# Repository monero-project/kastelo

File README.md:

# Kastelo
This is the project to create an official Monero Hardware Wallet

1. [Safe, Vault](https://en.wikipedia.org/wiki/Esperanto), a place to store valuables
2. An open hardware Monero wallet

## Are you a tester looking for FW?
Please go to firmware/monezor and read the README there

## Disclaimers
- No hardware available
- Currently in the design and pre-fabrication stage

## Documentation
- Project documentation is being written
- [Moneropedia](https://getmonero.org/knowledge-base/moneropedia/) is recommended for a general introduction to the Monero-verse

## Developers
- Contributing advice is found in CONTRIBUTING.md (please review before submitting a pull request)

### Project Management
Follow the engineering pace of our project at:

[https://taiga.getmonero.org/project/michael-rfc-hwallet-1-implementation/](https://taiga.getmonero.org/project/michael-rfc-hwallet-1-implementation/)

## Support
- IRC: [Freenode](irc://chat.freenode.net/#monero-hardware/)
- [Monero StackExchange](https://monero.stackexchange.com/)
- [Mattermost](https://mattermost.getmonero.org/monero/channels/monerohardware/)

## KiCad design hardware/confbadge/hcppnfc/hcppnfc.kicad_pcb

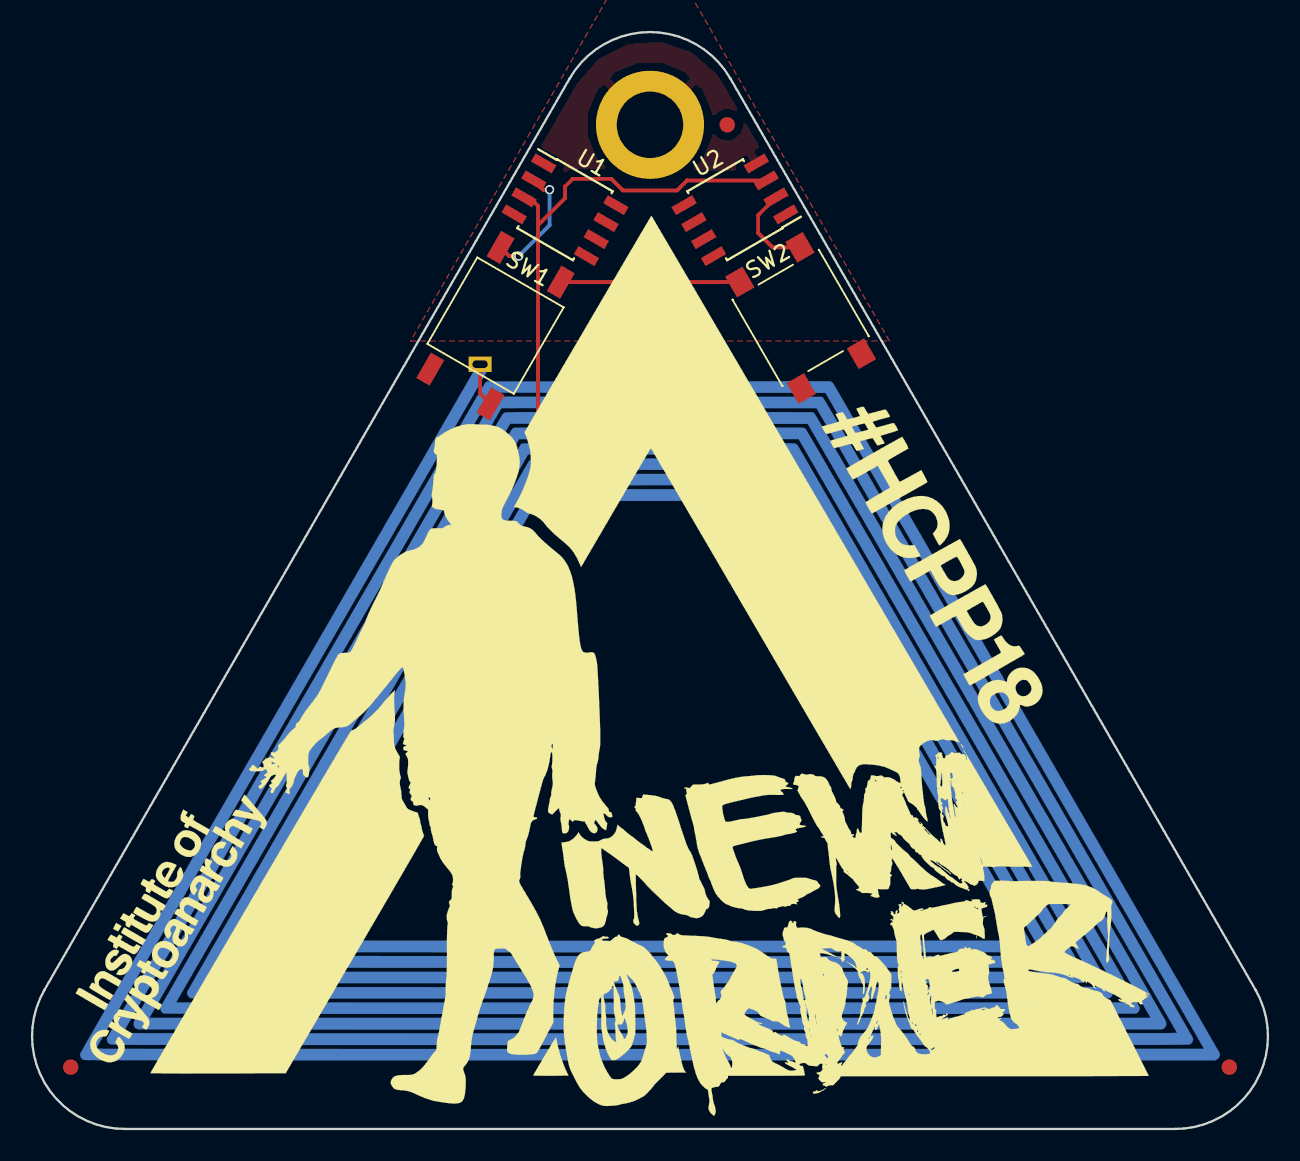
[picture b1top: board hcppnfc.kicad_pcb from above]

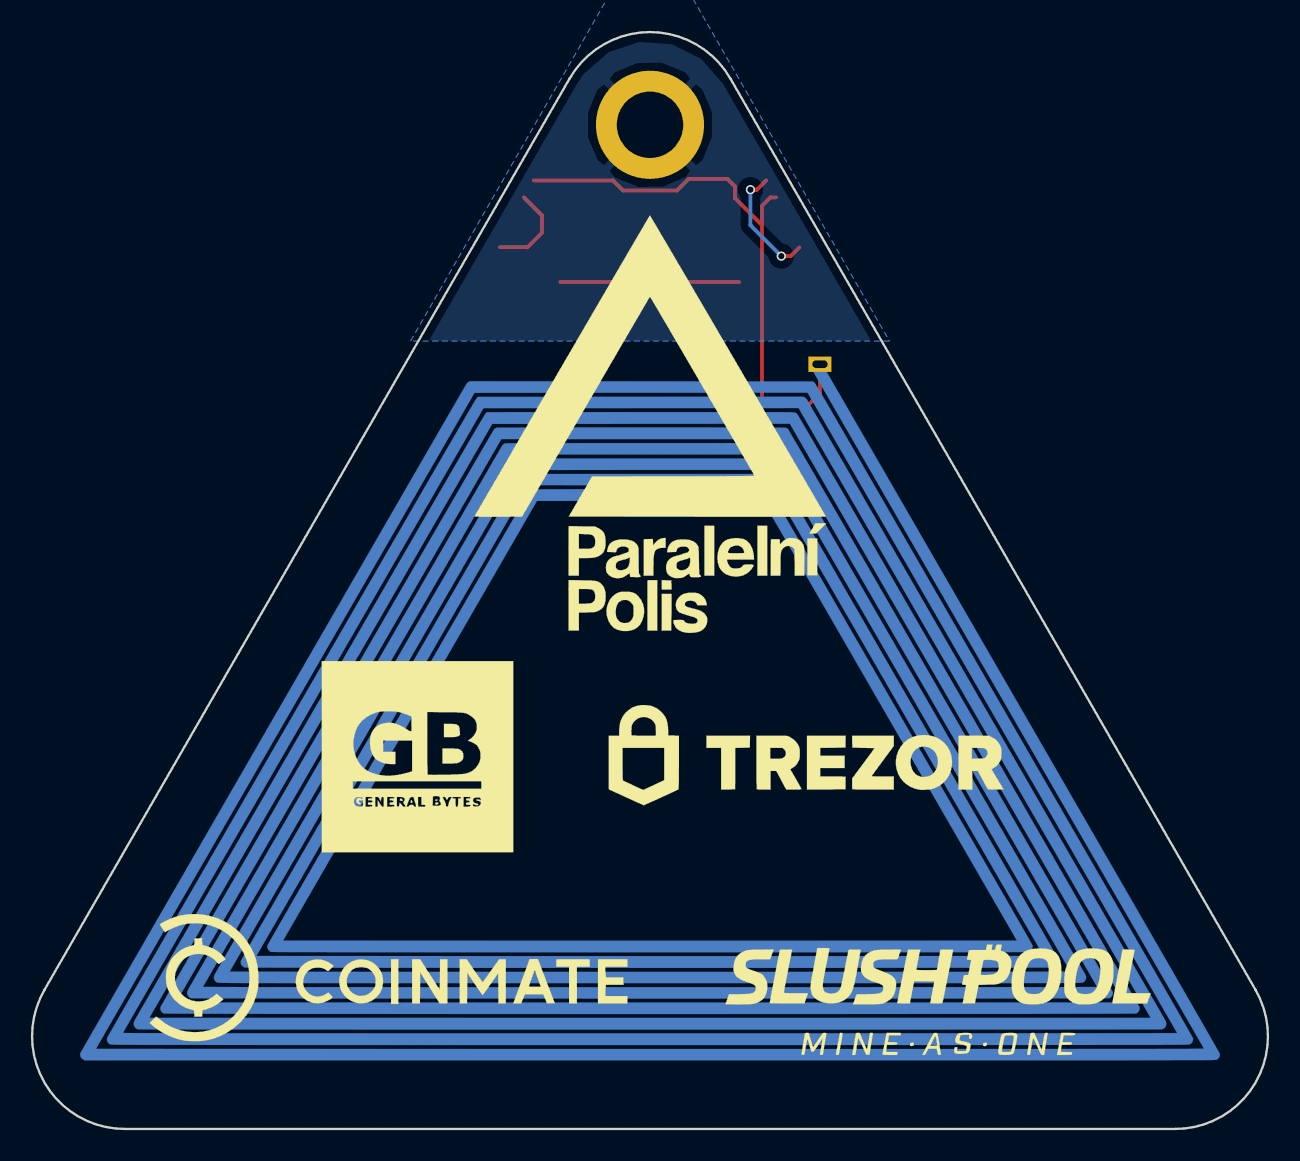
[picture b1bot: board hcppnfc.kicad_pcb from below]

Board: 2 copper layers, 80.0 x 71.0 mm, 13 parts (2 on the bottom side), 6 nets.

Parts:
AE1: Antenna_Loop; NFCAntennatall
FID1, FID2, FID3: Dummy_FIDUCIAL_Passermarke_Type1_RevE_Date16Nov20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; Fiducial_1mm_Dia_2mm_Outer
GFX*: ART_TRIANGLE; HCPPNewordtri
GFX*#2: ART_CONFYEAR; HCPPNewordconf
GFX*#3: ART_INSTCRYP; HCPPNewordinst
LOGO*: LOGO; HCPPSponsors
MH1: DUMMY_MOUNTING-HOLE_RevE_Date22jun2010; MountingHole_4.3mm_M4_ISO14580_Pad
SW1: SW_SPST; SW_SPST_K21102SP
SW2: SW_SPST; SW_SPST_PTS645
U1, U2: M24SR02-YMN; SOIC-8_3.9x4.9mm_Pitch1.27mm

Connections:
/ANTCON: AE1.2, U1.3, U2.3
GND: MH1.1, U1.4, U2.4
unnamed: AE1.1, SW1.1, SW2.1
unnamed: SW1.2, U1.2
unnamed: SW2.2, U2.2
VCC: U1.8, U2.8

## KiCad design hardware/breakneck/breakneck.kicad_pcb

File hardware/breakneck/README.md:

# Hardware Breakneck Design

The Breakneck design includes rich features as expected in a developer edition hardware wallet.

## Getting Started

The Breakneck design consists of several files, some which are not tracked in revision control but are part of [project releases](https://github.com/monero-project/kastelo/releases/).

* breakneck.pro (KiCad project)
* breakneck.sch (KiCad schematic)
* breakneck.kicad_pcb (KiCad layout)
* libraries (KiCad libraries)

Fabrication subdirectories contain files meant for printing, assembly, and other production work.

* billofmat (Bill of materials generated from breakneck.sch)
* fabpanel (Gerber files for printing panelized PCBs)
* fabraster (3D rendition of a single PCB layout)
* fabsingle (Gerber files for printing single PCBs)
* fabvector (Vector files useful for mechanical engineering)

Other subdirectories exist to provide conveniently formatted files generated from source.

* release (Tested distribution release files containing change logs)
* schematic (Copy of breakneck.sch converted to common graphic formats)

A Makefile serves project management tasks allowing for scripting and automation.

* Makefile (A GNU Makefile facilitating command line project tasks)

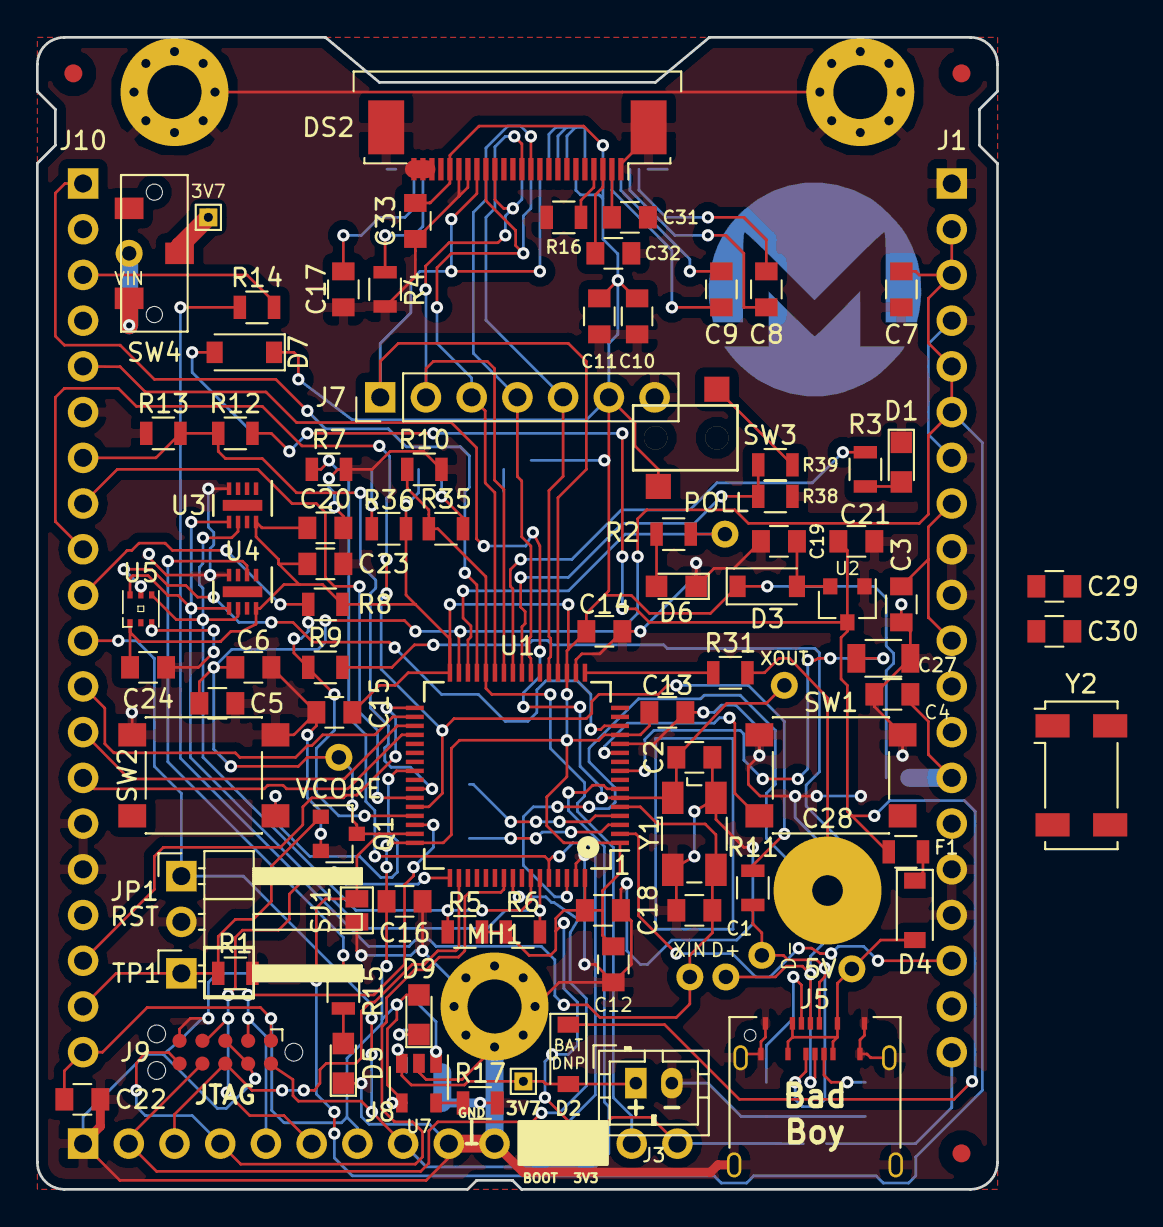
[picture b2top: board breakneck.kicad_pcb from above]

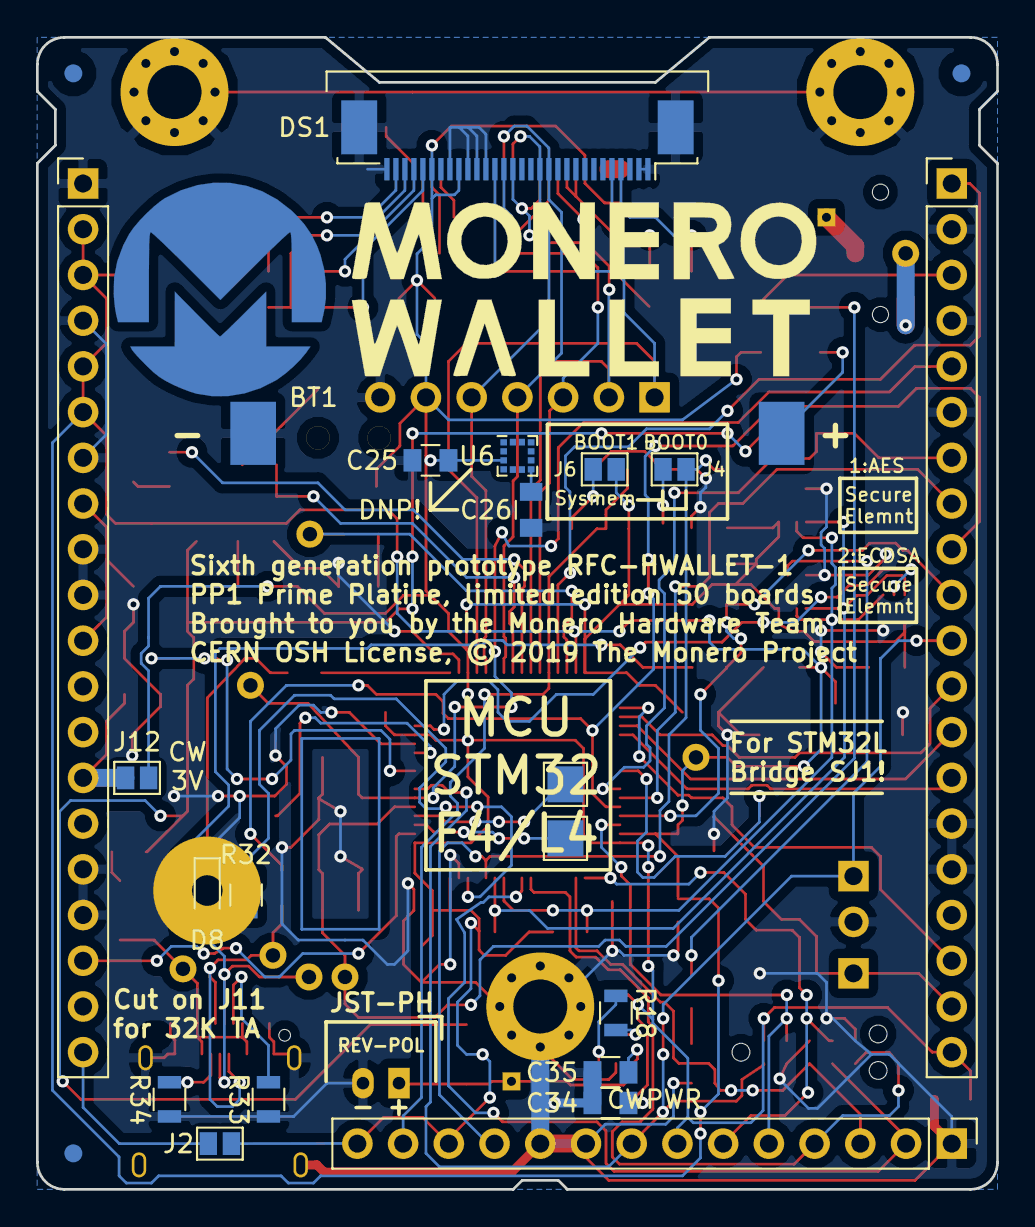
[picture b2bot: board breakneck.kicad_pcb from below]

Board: 2 copper layers, 53.3 x 64.0 mm, 124 parts (25 on the bottom side), 80 nets.

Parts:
3V7, 3V7#2: 3V7; TestPoint_THTPad_1.0x1.0mm_Drill0.5mm
5V: 5V; Measurement_Point_Round-TH_Small
BT1: Battery_Cell; Keystone_1058_1x2032-CoinCell
C1, C2: 12pF; C_0805
C3, C4, C7, C10, C12, C13, C14, C15, C16, C18, C20, C22, C23, C24, C25, C26: 100nF; C_0805
C5, C6, C17, C31: 2.2uF; C_0805
C8, C9, C11, C19, C21, C33: 1uF; C_0805
C27: 47nF; C_1206
C28: SW_Captouch; Captouch_Backlight_Circle_6mm
C29, C30: 4.3pF; C_0805
C32, C34, C35: 4.7uF; C_0805
D1: YELLOW; LED_0805
D2, D3, D4, D7: D_Schottky; D_SOD-123
D5: RED; LED_0805
D6, D9: LED; LED_0805
D8: WHITE; LED_0805
D+: DATA+; Measurement_Point_Round-TH_Small
D-: DATA-; Measurement_Point_Round-TH_Small
DS1: SSD1306; Eastrising_ER-CON30HT-1_01x30_P0.50mm
DS2: ER-CON24; Eastrising_ER-CON24HT-1_01x24_P0.50mm
F1: PTC; R_0805
FID1, FID2, FID3, FID4, FID5, FID6: Fiducial-PCB; Fiducial_1mm_Dia_2.54mm_Outer_CopperTop
J1: CONN_EAST; Pin_Header_Straight_1x20_Pitch2.54mm
J2, J4, J6, J12: GS2
J3: CONN_01X02; JST_PH_B2B-PH-K_02x2.00mm_Straight
J5: USB_C_Rcpt_Min; USBC_Rcpt_Min_12401610E4-2A
J7: CONN_OLED; Socket_Strip_Straight_1x07_Pitch2.54mm
J8: CONN_SOUTH; Pin_Header_Straight_1x14_Pitch2.54mm
J9: CONN_JTAG; Tag-Connect_TC2050-IDC-NL
J10: CONN_WEST; Pin_Header_Straight_1x20_Pitch2.54mm
JP1: Jumper; Pin_Header_Angled_1x02_Pitch2.54mm
LOGO1: Monerologo-mid; MoneroCircleCombi
MH1, MH2, MH3: Mountinghole-440; MountingHole_3mm_Pad_Via
POLL: TEST; Measurement_Point_Round-TH_Small
Q1: MOSFET; SOT-23
R1, R7, R10: 10K; R_0805
R2, R3, R15, R32: 150; R_0805
R4, R16: 390K; R_0805
R5, R6: 3.9K; R_0805
R8: 1.5K; R_0805
R9, R11: 22; R_0805
R12: 12K; R_0805
R13: 22K; R_0805
R14: 100; R_0805
R17: 2K; R_0805
R18: 470; R_0805
R31: 1K; R_0805
R33, R34: 5.1K; R_0805
R35, R36, R39: 510; R_0805
R38: 100K; R_0805
REF7, REF8: TestPoint_Pad_2.0x2.0mm
SJ1: Solderjumper; GS2
SW1, SW2: SW_SPST; SW_SPST_PTS645
SW3: SW_SPST; SW_SPST_ESE11MV1
SW4: SW_SPDT; SW_SPDT_CLSB-12A
TP1: GLITCH; Pin_Header_Angled_1x01_Pitch2.54mm
U1: STM32F405RGTx; LQFP-64_10x10mm_Pitch0.5mm
U2: LN6206P33M_SOT23; SOT-23
U3: ATECC608A; DFN-8-1EP_2x3mm_Pitch0.5mm
U4: ATAES132A; DFN-8-1EP_2x3mm_Pitch0.5mm
U5: LTR303ALS; ChipLED-6_2x2mm
U6: BMA280; LGA-12_2x2mm_P0.5mm
U7: MCP73831-2-OT; SOT-23-5
VCORE: VCORE; Measurement_Point_Round-TH_Small
VIN: VIN; Measurement_Point_Round-TH_Small
XIN: CRYSTIN; Measurement_Point_Round-TH_Small
XOUT: CRYSTOUT; Measurement_Point_Round-TH_Small
Y1: Crystal_GND24; Crystal_SMD_Abracon_ABM3B-4pin_5.0x3.2mm
Y2: Crystal; Crystal_SMD_Abracon_ABS25-4Pin_8.0x3.8mm

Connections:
+1V2: C5.1, C6.1, C7.1, J1.2, J1.3, J1.5, J1.6, Q1.3, SJ1.1, U1.31, U1.47, VCORE.1
+3V3: C10.1, C11.1, C12.1, C13.1, C14.1, C15.1, C16.1, C18.1, C20.1, C22.1, C23.1, C24.1, C25.1, C26.2, C33.1, C34.1, D3.1, D7.1, D9.2, DS1.6, DS1.9, DS2.5, J2.2, J6.2, J7.6, J8.7, J8.12, J8.14, J9.1, J10.20, J12.2, R5.1, R6.1, R8.2, R36.1, SW3.2, U1.1, U1.13, U1.19, U1.32, U1.48, U1.64, U3.8, U4.8, U5.1, U6.3, U6.7, U6.11, U7.4
+5V: C21.1, D2.1, F1.1, R12.2, U2.3
/BLOAD: J4.2, J8.11, R7.1, U1.60
/CTCH: R31.1, U1.17
/CTLED: R32.1, U1.62
/CTSMP: C27.1, U1.9
/GLITCH: J10.19, Q1.1, R1.1, TP1.1
/I2C_SCL: R5.2, U1.58, U3.6, U4.6, U5.4, U6.12
/I2C_SDA: R6.2, U1.59, U3.5, U4.5, U5.6, U6.2
/INT1: U1.15, U6.5
/INT2: U1.16, U6.6
/JTAG_TCK: J8.6, J9.4, U1.49
/JTAG_TDI: J8.3, J9.8, U1.50
/JTAG_TDO: J8.4, J9.6, U1.55
/JTAG_TMS: J8.5, J9.2, U1.46
/JTAG_TRST: J8.2, J9.7, U1.56
/OLED_D0: DS1.18, DS2.13, J7.5, U1.21
/OLED_D1: DS1.19, DS2.14, J7.4, U1.23
/OLED_DC: DS1.15, DS2.10, J7.2, U1.26
/OLED_~CS~: DS1.13, DS2.8, J7.1, U1.20
/OLED_~RES~: DS1.14, DS2.9, J7.3, U1.27
/OSC_IN: C1.1, R14.2, U1.5, XIN.1, Y1.3
/OSC_OUT: C2.2, J10.5, U1.6, XOUT.1, Y1.1
/RESET: J8.8, J9.10, J10.11, JP1.1, U1.7
/SPI_CS: J10.18, U1.33
/SPI_MISO: J10.13, U1.35
/SPI_MOSI: J10.14, U1.36
/SPI_SCK: J10.12, U1.34
/UART_RX: J10.8, U1.43
/UART_TX: J10.7, R12.1, R13.2, U1.42
/USB_N: J10.9, R11.2, U1.44
/USB_P: J10.10, R8.1, R9.2, U1.45
GND: BT1.2, C1.2, C2.1, C3.1, C4.1, C5.2, C6.2, C7.2, C10.2, C11.2, C12.2, C13.2, C14.2, C15.2, C16.2, C17.2, C18.2, C19.2, C20.2, C21.2, C22.2, C23.2, C24.2, C25.2, C26.1, C27.2, C29.2, C30.2, C31.2, C32.2, C33.2, C34.2, C35.2, D1.1, D5.1, D6.1, D8.1, DS1.1, DS1.8, DS1.10, DS1.11, DS1.12, DS1.29, DS1.30, DS2.1, DS2.2, DS2.3, DS2.6, DS2.7, DS2.24, J1.1, J1.4, J1.7, J1.9, J1.10, J1.16, J1.17, J3.2, J5.A1, J5.A12, J5.B1, J5.B12, J5.S1, J7.7, J8.1, J8.9, J8.10, J9.3, J9.5, J9.9, J10.2, J10.4, J10.6, J10.15, J10.16, JP1.2, MH1.1, MH2.1, MH3.1, Q1.2, R1.2, R4.1, R7.2, R10.2, R13.1, R16.2, R17.2, R33.1, R34.1, R38.2, SJ1.2, SW1.1, SW2.1, U1.12, U1.18, U1.63, U2.1, U3.4, U4.4, U5.3, U6.1, U6.8, U6.9, U7.2, Y1.2, Y1.4
unnamed: BT1.1, D7.2
unnamed: C3.2, J1.8, J1.11
unnamed: C4.2, J1.14, J12.1
unnamed: C8.1, DS1.2
unnamed: C8.2, DS1.3
unnamed: C9.1, DS1.4
unnamed: C9.2, DS1.5
unnamed: C17.1, DS1.27
unnamed: C19.1, D3.2, U2.2
unnamed: C28.1, R31.2
unnamed: C29.1, REF8.1, U1.3, Y2.1
unnamed: C30.1, REF7.1, U1.4, Y2.2
unnamed: C31.1, DS2.23
unnamed: C32.1, DS2.22
unnamed: C35.1, J3.1, SW4.3, U7.3
unnamed: D1.2, R3.2
unnamed: 3V7.1, 3V7#2.1, D2.2, SW4.2
unnamed: D4.1, F1.2
unnamed: 5V.1, D4.2, J5.A4, J5.A9, J5.B4, J5.B9
unnamed: D5.2, R15.2
unnamed: D6.2, R2.1
unnamed: D8.2, R32.2
unnamed: D9.1, R18.2
unnamed: DS1.26, R4.2
unnamed: DS2.21, R16.1
unnamed: J1.18, U1.2
unnamed: J1.20, J2.1
unnamed: J4.1, R36.2
unnamed: J5.A5, R33.2
unnamed: D+.1, J5.A6, J5.B6, R9.1
unnamed: D-.1, J5.A7, J5.B7, R11.1
unnamed: J5.B5, R34.2
unnamed: J6.1, R35.2
unnamed: J8.13, R10.1, R35.1, U1.28
unnamed: J10.1, U1.29
unnamed: J10.3, R14.1
unnamed: POLL.1, R2.2, U1.30
unnamed: R3.1, U1.25
unnamed: R15.1, U4.2
unnamed: R17.1, U7.5
unnamed: R18.1, U7.1
unnamed: R38.1, R39.2, U1.24
unnamed: R39.1, SW3.1
unnamed: SW1.2, U1.11
unnamed: SW2.2, U1.40
unnamed: U1.14, U5.5

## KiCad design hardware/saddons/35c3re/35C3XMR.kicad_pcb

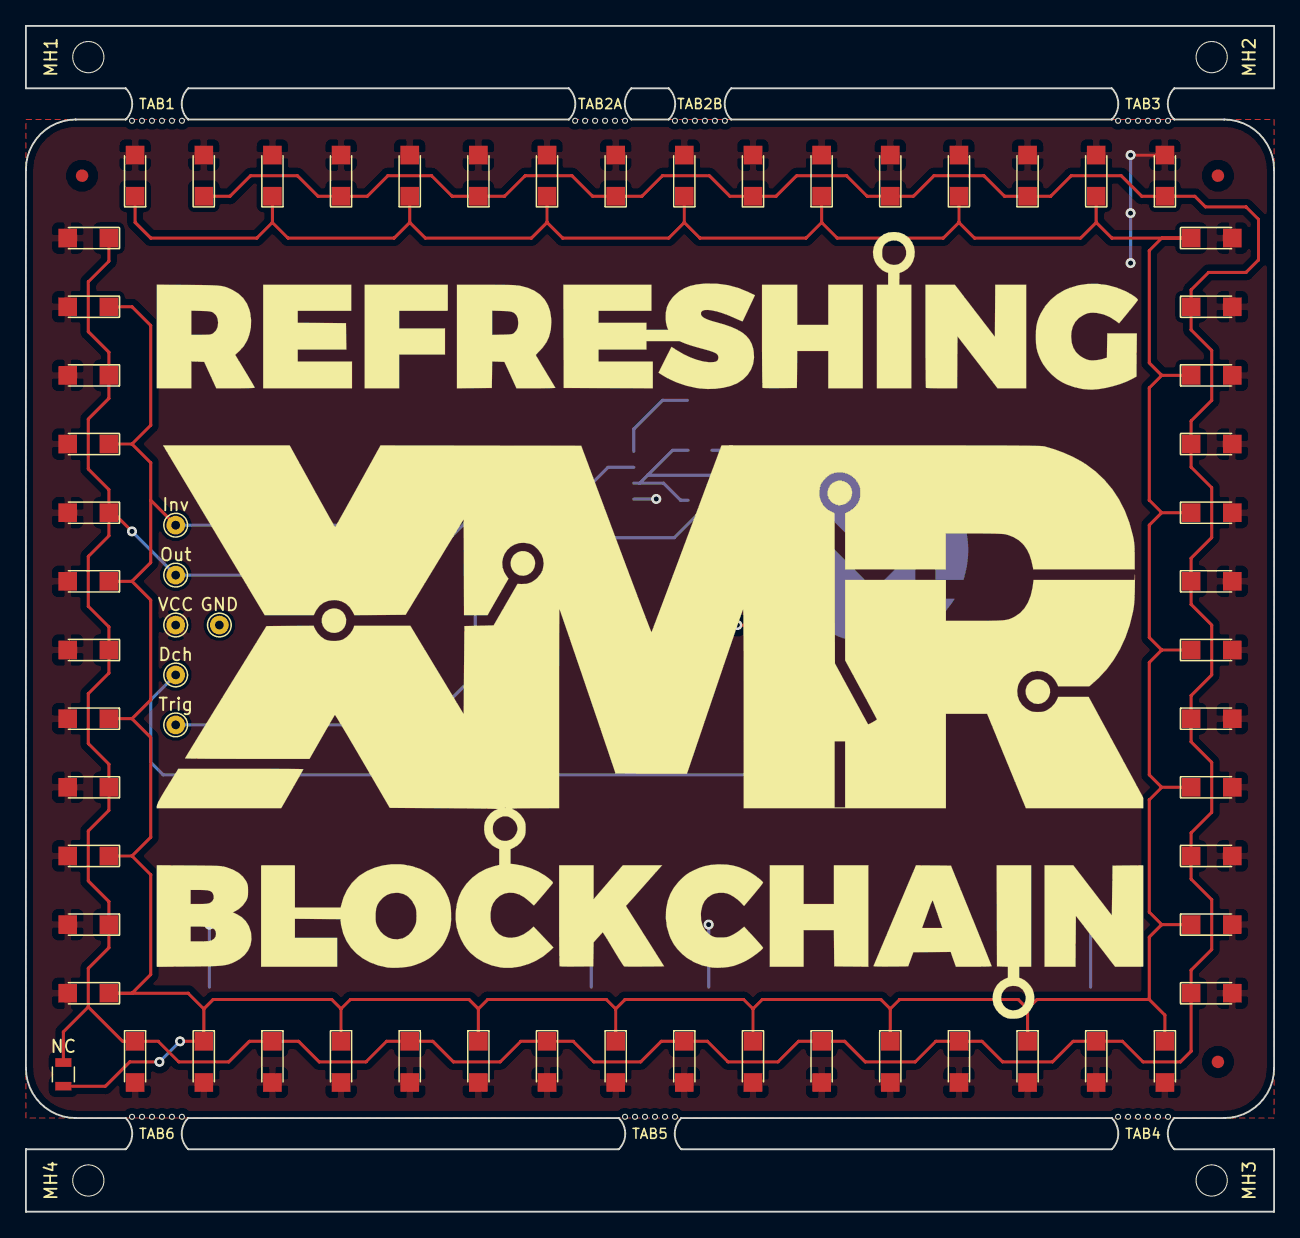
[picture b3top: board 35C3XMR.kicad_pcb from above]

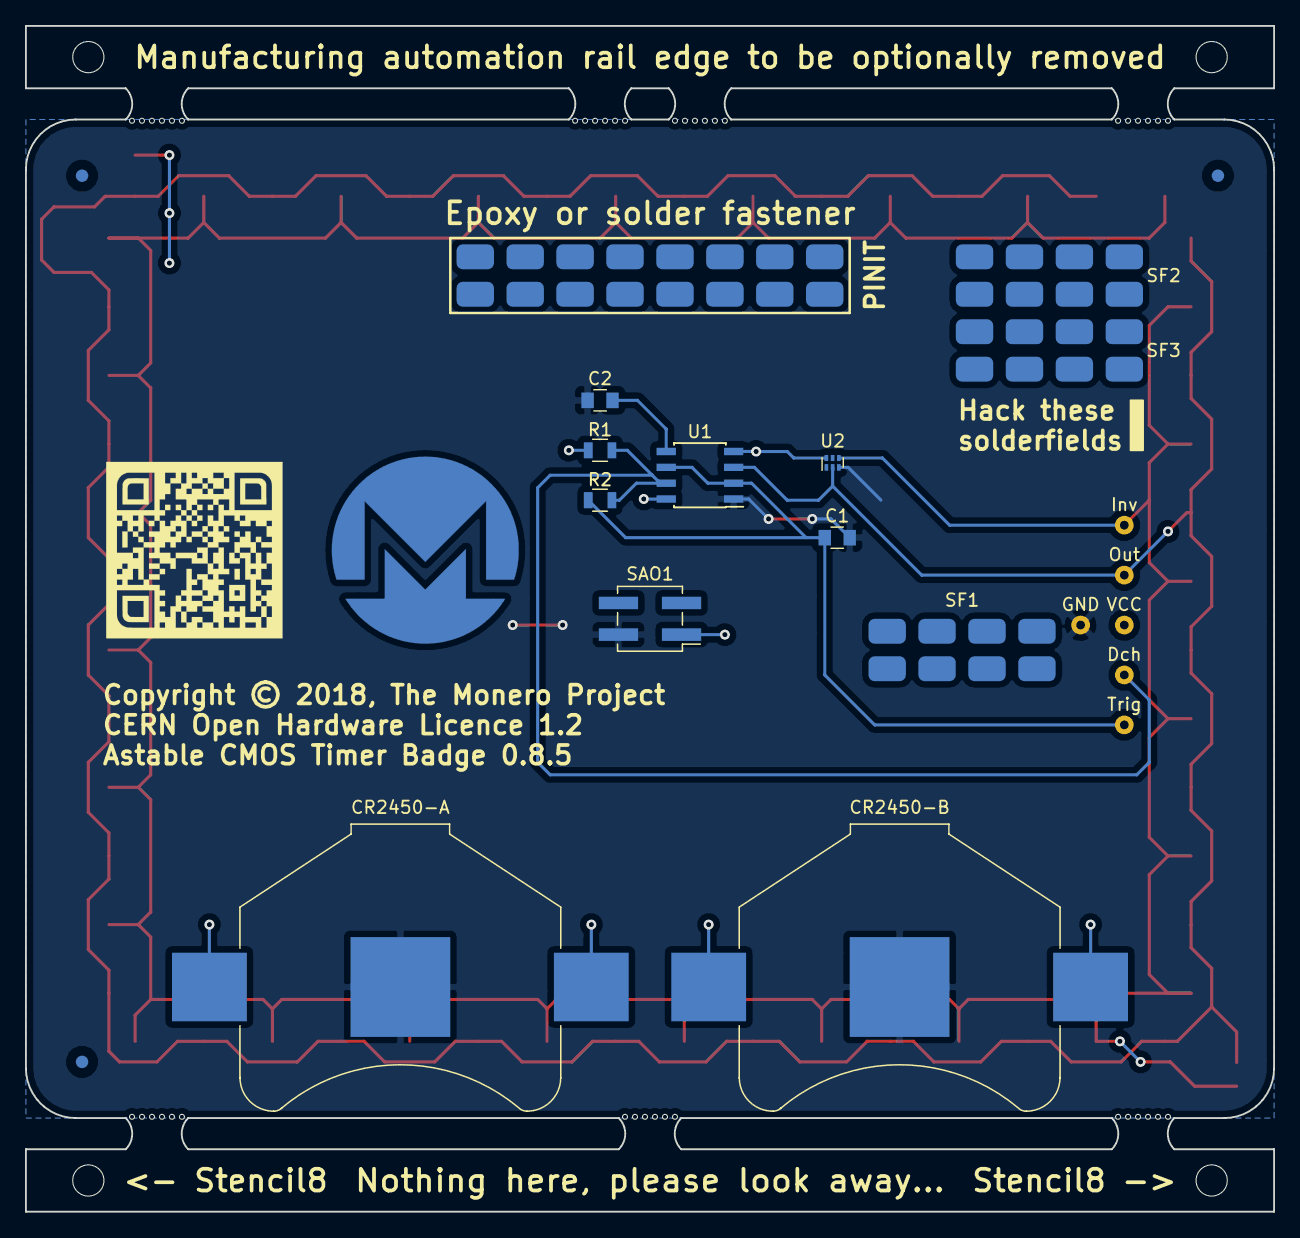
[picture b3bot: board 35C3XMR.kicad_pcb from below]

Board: 2 copper layers, 100.0 x 95.0 mm, 97 parts (19 on the bottom side), 7 nets.

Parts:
C1: 4,7uF; C_0805
C2: ,01uF; C_0805
CR2450-A, CR2450-B: Battery_Cell; BatteryHolder_Keystone_3008_1x2450
D1, D2, D3, D4, D5, D6, D7, D8, D9, D10, D11, D12, D13, D14, D15, D16, D17, D18, D19, D20, D21, D22, D23, D24, D25, D26, D27, D28, D29, D30, D31, D32, D33, D34, D35, D36, D37, D38, D39, D40, D41, D42, D43, D44, D45, D46, D47, D48, D49, D50, D51, D52, D53, D54, D55, D56: LED; LED_1206
Dch: TEST; TestPoint_THTPad_D1.5mm_Drill0.7mm
FID1, FID3, FID5: FiducialPassermarke-Top; Fiducial_1mm_Dia_2.54mm
FID2, FID4, FID6: FiducialPassermarke-Bot; Fiducial_1mm_Dia_2.54mm
G1: QRCOD; Kastelospecsqr
GND: TEST; TestPoint_THTPad_D1.5mm_Drill0.7mm
Inv: TEST; TestPoint_THTPad_D1.5mm_Drill0.7mm
LOGO1: 35C3Logo-funny; 35C3Funny
LOGO2: Moneroball; Moneroball_15mm
MH1, MH2, MH3, MH4: MountingHole_2.5mm
NC: Jumper; R_0805
Out: TEST; TestPoint_THTPad_D1.5mm_Drill0.7mm
R1: 10K; R_0805
R2: 100K; R_0805
SAO1: Shitty_conn; PinHeader_2x02_P2.54mm_Vertical_SMD
SF1, SF2, SF3, SF4, SF5: Soldfeld; Solderarea
TAB1, TAB2A, TAB2B, TAB3, TAB4, TAB5, TAB6: Panel_Mousetab_25mm_Single
Trig: TEST; TestPoint_THTPad_D1.5mm_Drill0.7mm
U1: TLC555; SOIC-8_3.9x4.9mm_P1.27mm
U2: NC7SZ04L6X; Fairchild_MicroPak-6_1.0x1.45mm_P0.5mm
VCC: TEST; TestPoint_THTPad_D1.5mm_Drill0.7mm

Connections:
+3V3: CR2450-A.1, CR2450-B.1, D1.2, D2.2, D3.2, D4.2, D5.2, D6.2, D7.2, D8.2, D9.2, D10.2, D11.2, D12.2, D13.2, D14.2, D15.2, D16.2, D17.2, D18.2, D19.2, D20.2, D21.2, D22.2, D23.2, D24.2, D25.2, D26.2, D27.2, D28.2, D29.2, D30.2, D31.2, D32.2, D33.2, D34.2, D35.2, D36.2, D37.2, D38.2, D39.2, D40.2, D41.2, D42.2, D43.2, D44.2, D45.2, D46.2, D47.2, D48.2, D49.2, D50.2, D51.2, D52.2, D53.2, D54.2, D55.2, D56.2, R1.2, SAO1.1, U1.4, U1.8, U2.6, VCC.1
GND: C1.2, C2.2, CR2450-A.2, CR2450-B.2, GND.1, SAO1.2, U1.1, U2.3
unnamed: C1.1, R2.2, Trig.1, U1.2, U1.6
unnamed: C2.1, U1.5
unnamed: D1.1, D3.1, D5.1, D7.1, D9.1, D11.1, D13.1, D15.1, D17.1, D19.1, D21.1, D23.1, D25.1, D27.1, D29.1, D31.1, D33.1, D35.1, D37.1, D39.1, D41.1, D43.1, D45.1, D47.1, D49.1, D51.1, D53.1, D55.1, Inv.1, NC.2, U2.4
unnamed: D2.1, D4.1, D6.1, D8.1, D10.1, D12.1, D14.1, D16.1, D18.1, D20.1, D22.1, D24.1, D26.1, D28.1, D30.1, D32.1, D34.1, D36.1, D38.1, D40.1, D42.1, D44.1, D46.1, D48.1, D50.1, D52.1, D54.1, D56.1, NC.1, Out.1, U1.3, U2.2
unnamed: Dch.1, R1.1, R2.1, U1.7

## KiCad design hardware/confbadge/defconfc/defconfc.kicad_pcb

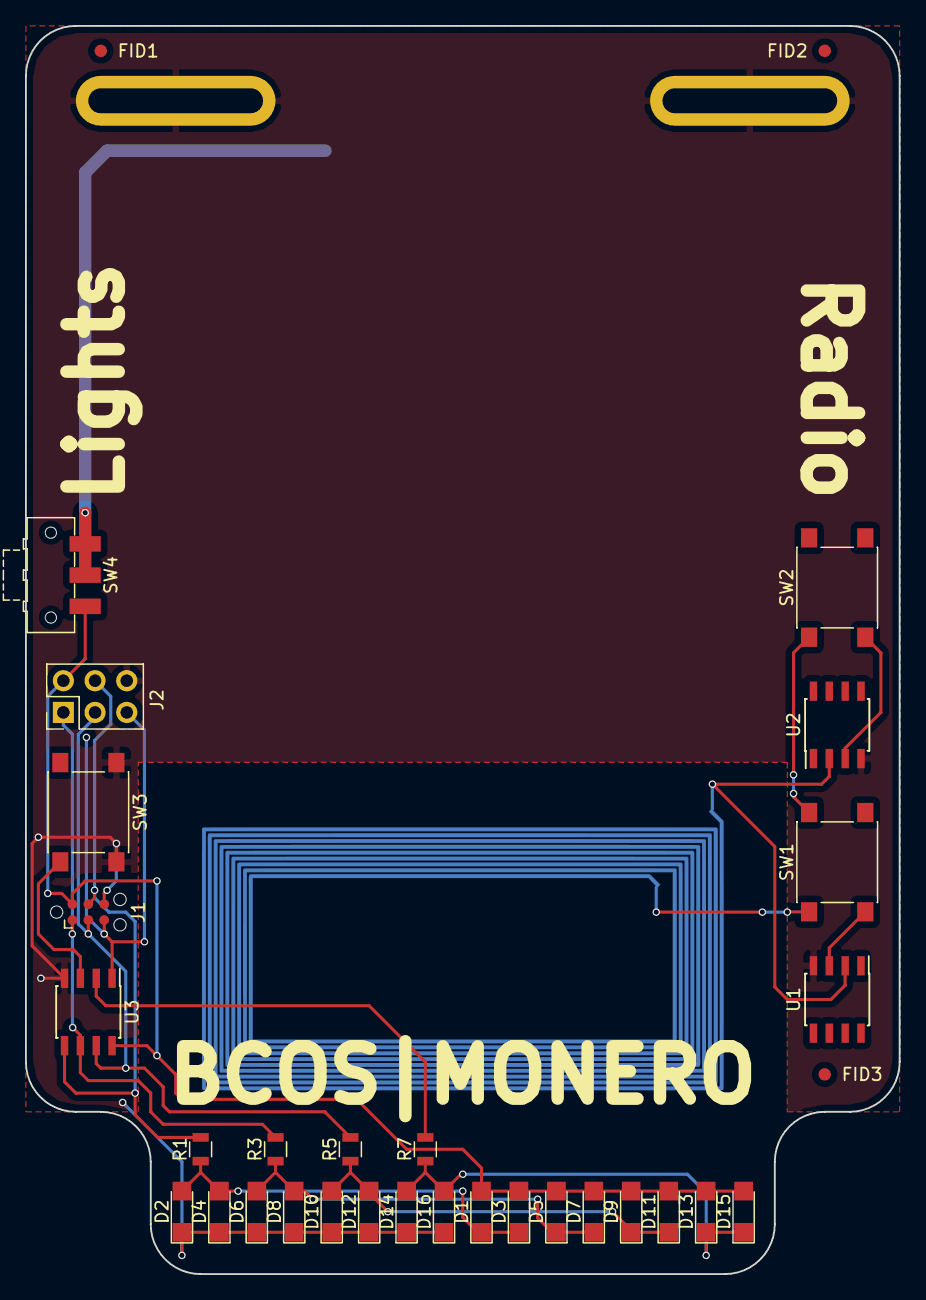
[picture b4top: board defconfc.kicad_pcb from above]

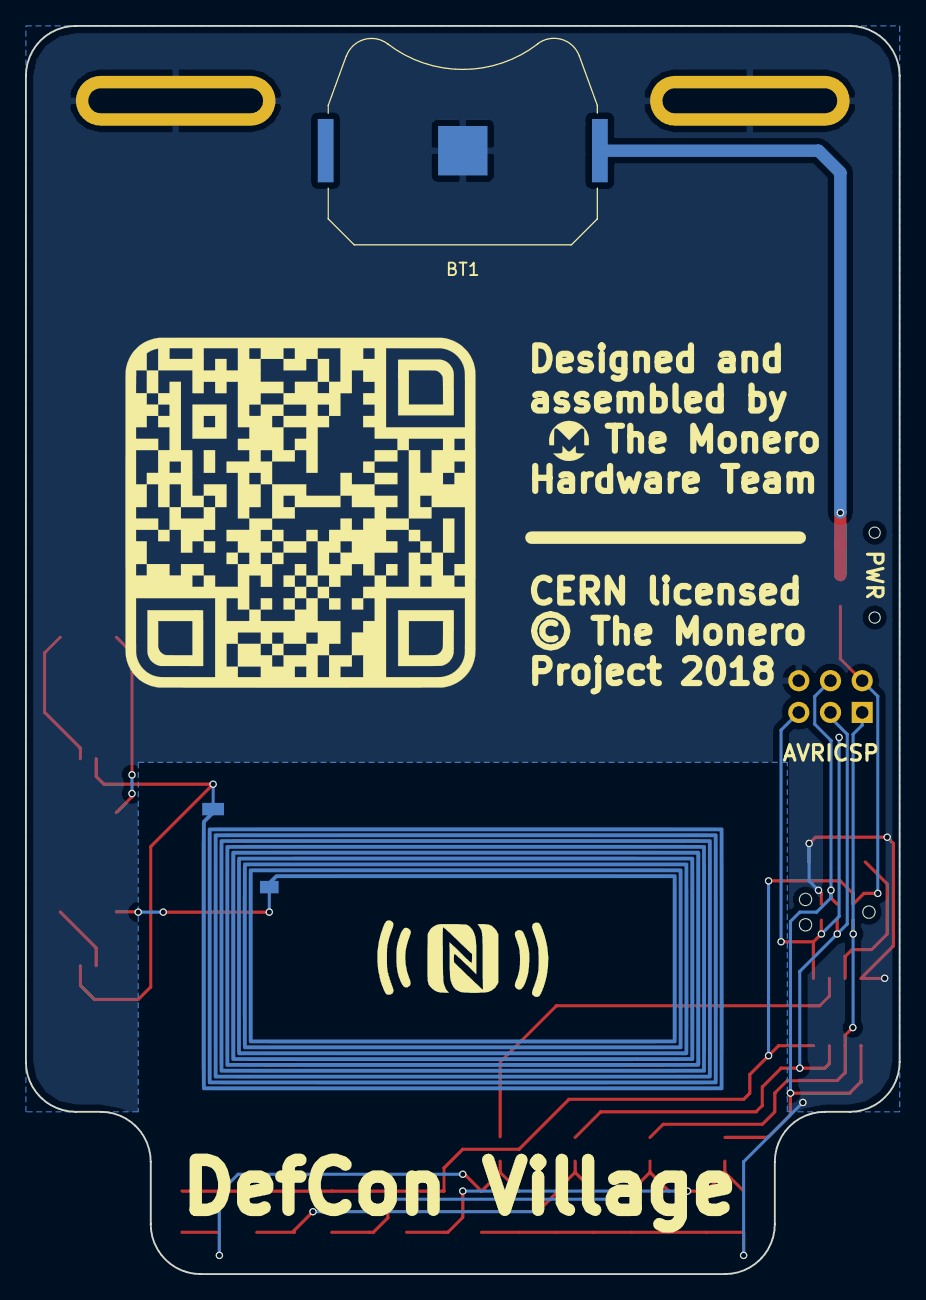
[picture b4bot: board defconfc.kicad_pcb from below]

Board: 2 copper layers, 70.0 x 100.0 mm, 39 parts (5 on the bottom side), 17 nets.

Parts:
AE1: Antenna_PCB; NFCAntennaloop
BT1: Battery_Cell; Keystone_3034_1x2032-Coincell
D1, D2, D3, D4, D5, D6, D7, D8, D9, D10, D11, D12, D13, D14, D15, D16: LED; LED_1206
FID1, FID2, FID3: Fiducial_Passermarke; Fiducial_1mm_Dia_2mm_Outer
G1: NFCRadiate; NFCGraphicsrear
G2: Kastelospecs; Kastelospecsqrcode
J1: Conn_02x03_Odd_Even; Tag-Connect_TC2030-IDC-NL
J2: Conn_02x03_Odd_Even; Pin_Header_Straight_2x03_Pitch2.54mm
L2: Graphbrand; Monerologokreis
LH1, LH2: Mounting-Lanyard; LanyardHole_16mm_Pad
R1, R3, R5, R7: 220; R_0805
SW1, SW2, SW3: SW_SPST; SW_SPST_PTS645
SW4: SW_SPDT; SW_SPDT_CK-JS102011SAQN
U1, U2: M24SR16-YMN6T/2; SOIC-8_3.9x4.9mm_Pitch1.27mm
U3: ATTINY13A-SSU; SOIC-8_3.9x4.9mm_Pitch1.27mm

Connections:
GND: BT1.2, D2.1, D4.1, D6.1, D8.1, D10.1, D12.1, D14.1, D16.1, J1.6, J2.6, LH1.1, LH2.1, SW3.2, U1.4, U2.4, U3.4
MISO: J1.1, J2.1, R3.2, U3.6
MOSI: J1.4, J2.4, R1.2, U3.5
unnamed: AE1.1, U1.2, U2.2
unnamed: AE1.2, SW1.1, SW2.1
unnamed: BT1.1, SW4.1, SW4.2
unnamed: D1.1, D2.2, D3.1, D4.2, R1.1
unnamed: D5.1, D6.2, D7.1, D8.2, R3.1
unnamed: D9.1, D10.2, D11.1, D12.2, R5.1
unnamed: D13.1, D14.2, D15.1, D16.2, R7.1
unnamed: SW1.2, U1.3
unnamed: SW2.2, U2.3
unnamed: SW3.1, U3.3
PB3: R7.2, U3.2
RST: J1.5, J2.5, U3.1
SCK: J1.3, J2.3, R5.2, U3.7
VCC: D1.2, D3.2, D5.2, D7.2, D9.2, D11.2, D13.2, D15.2, J1.2, J2.2, SW4.3, U3.8

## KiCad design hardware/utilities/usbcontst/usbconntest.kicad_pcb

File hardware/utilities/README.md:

# Hardware Utilities Design

One paragraph of descriptive text.

## Getting Started

Example text to help understand contents and subdirectories.

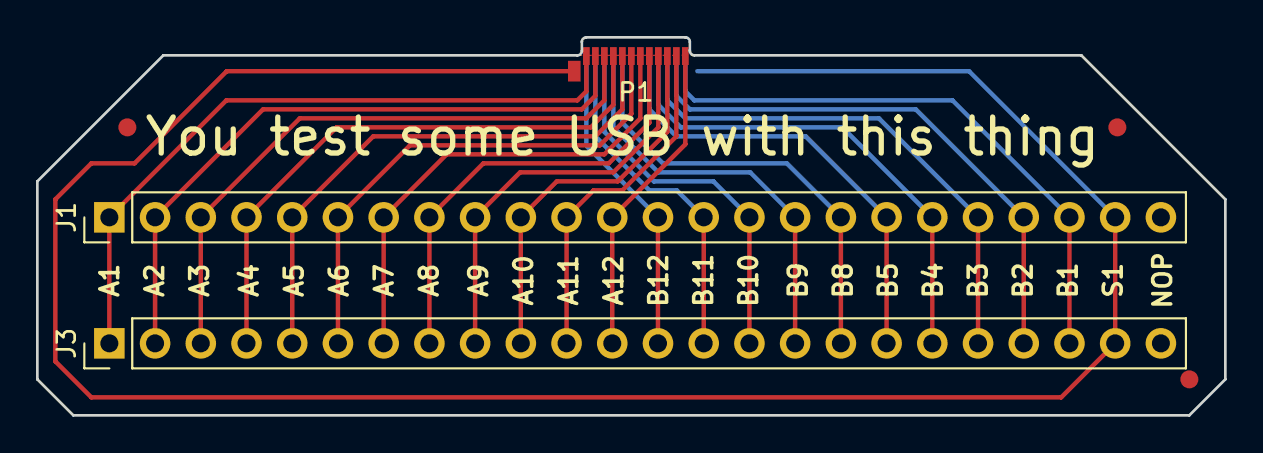
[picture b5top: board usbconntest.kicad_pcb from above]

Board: 2 copper layers, 66.0 x 21.0 mm, 6 parts (0 on the bottom side), 23 nets.

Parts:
FID1, FID2, FID3: Dummy_FIDUCIAL_Passermarke_Type1_RevE_Date16Nov20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; Fiducial_1mm_Dia_2mm_Outer
J1, J3: CONN_01X24; Pin_Header_Straight_1x24_Pitch2.54mm
P1: USB_C_Plug; USB_C_Plug_Molex_105444

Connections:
/A1: J1.1, J3.1, P1.A1
/A2: J1.2, J3.2, P1.A2
/A3: J1.3, J3.3, P1.A3
/A4: J1.4, J3.4, P1.A4
/A5: J1.5, J3.5, P1.A5
/A6: J1.6, J3.6, P1.A6
/A7: J1.7, J3.7, P1.A7
/A8: J1.8, J3.8, P1.A8
/A9: J1.9, J3.9, P1.A9
/A10: J1.10, J3.10, P1.A10
/A11: J1.11, J3.11, P1.A11
/A12: J1.12, J3.12, P1.A12
/B1: J1.22, J3.22, P1.B1
/B2: J1.21, J3.21, P1.B2
/B3: J1.20, J3.20, P1.B3
/B4: J1.19, J3.19, P1.B4
/B5: J1.18, J3.18, P1.B5
/B8: J1.17, J3.17, P1.B8
/B9: J1.16, J3.16, P1.B9
/B10: J1.15, J3.15, P1.B10
/B11: J1.14, J3.14, P1.B11
/B12: J1.13, J3.13, P1.B12
/S1: J1.23, J3.23, P1.S1

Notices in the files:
hardware/breakneck/breakneck.kicad_pcb:
Copyright © 2019, The Monero Project
CERN OSH License, © 2019 The Monero Project
hardware/confbadge/defconfc/defconfc.kicad_pcb:
Copyright © 2018, The Monero Project
© The Monero
hardware/saddons/35c3re/35C3XMR.kicad_pcb:
CERN Open Hardware Licence 1.2
